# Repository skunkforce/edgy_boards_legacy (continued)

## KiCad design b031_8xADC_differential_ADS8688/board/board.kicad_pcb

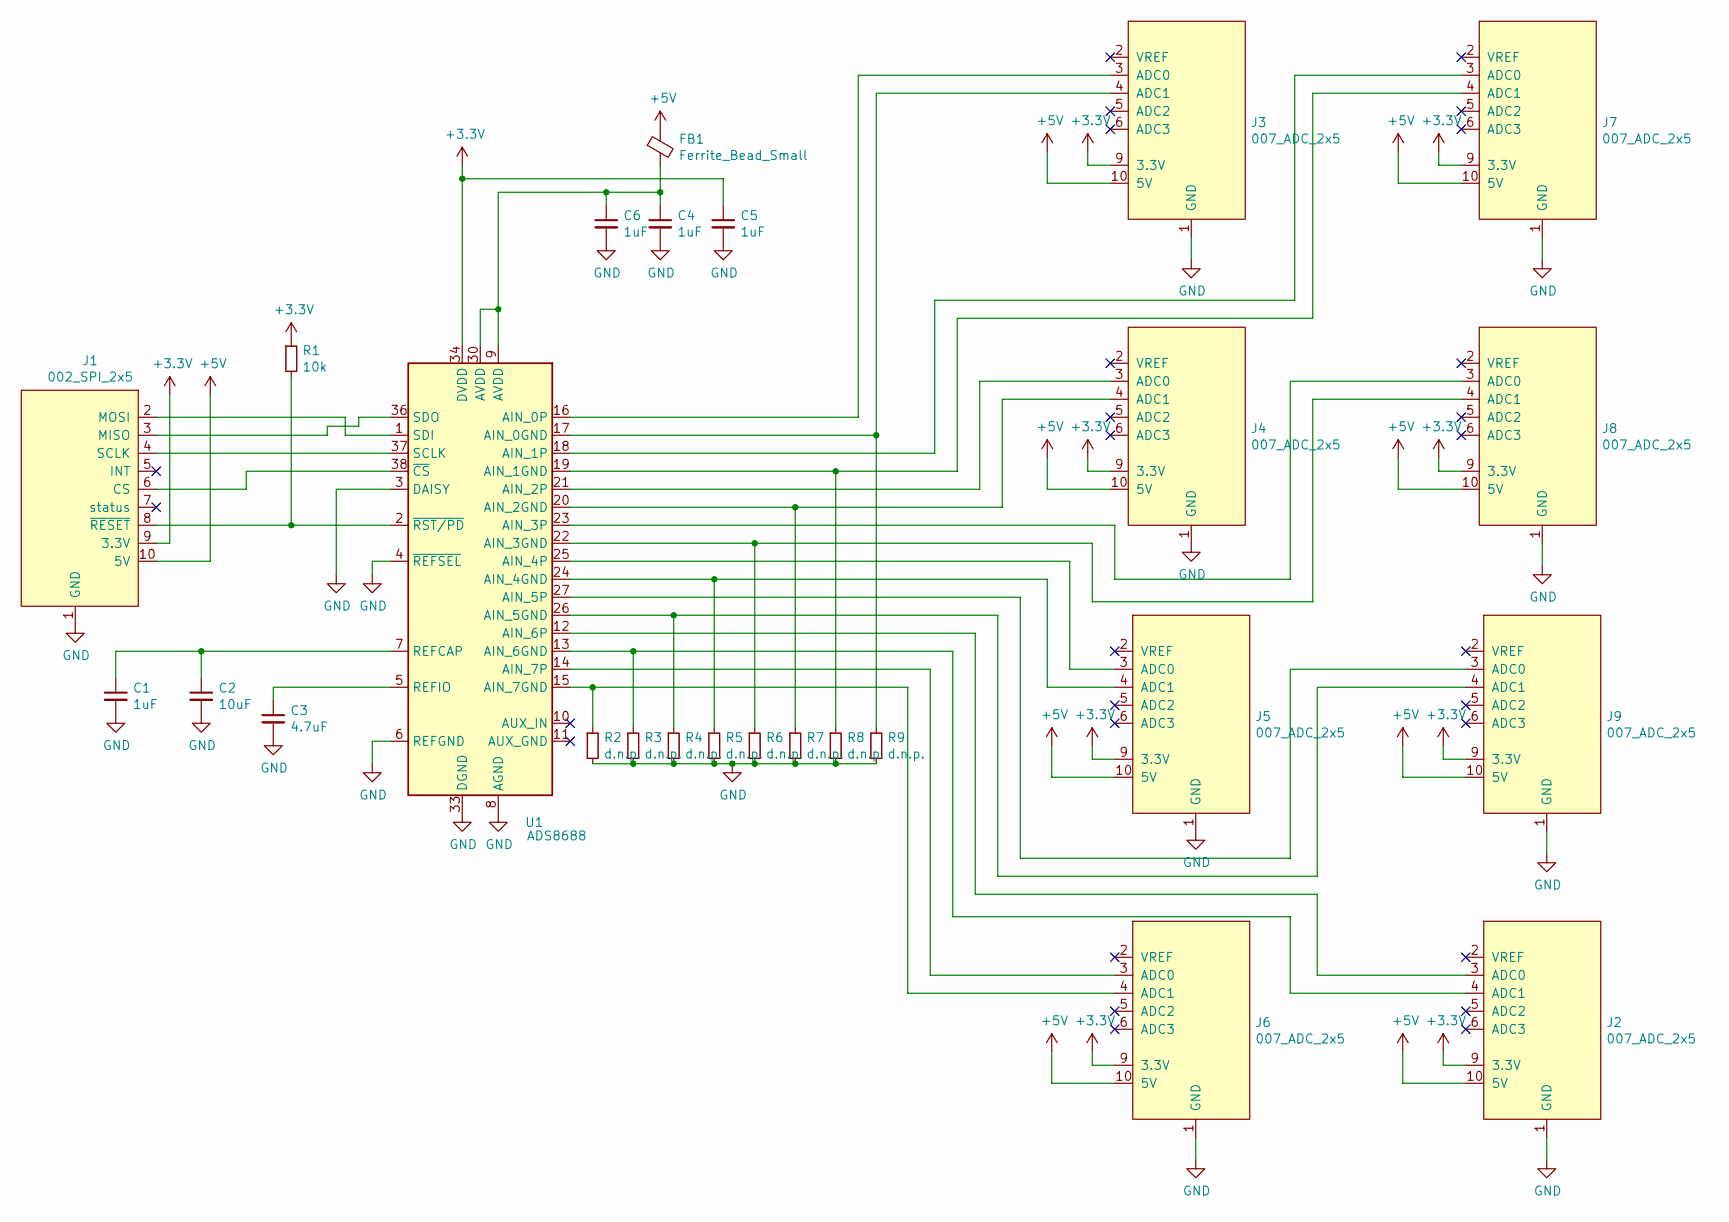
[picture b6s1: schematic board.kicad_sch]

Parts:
C1, C4, C5, C6: 1uF; C_0603_1608Metric
C2: 10uF; C_0603_1608Metric
C3: 4.7uF; C_0603_1608Metric
FB1: Ferrite_Bead_Small; L_0603_1608Metric
J1: 002_SPI_2x5; on_edge_2x05_device
J2, J3, J4, J5, J6, J7, J8, J9: 007_ADC_2x5; on_edge_2x05_host
R1: 10k; R_0603_1608Metric
R2, R3, R4, R5, R6, R7, R8, R9: d.n.p.; R_0603_1608Metric
U1: ADS8688; TSSOP-38_4.4x9.7mm_P0.5mm

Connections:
+3V3: C5.1, J1.9 (3.3V), J2.9 (3.3V), J3.9 (3.3V), J4.9 (3.3V), J5.9 (3.3V), J6.9 (3.3V), J7.9 (3.3V), J8.9 (3.3V), J9.9 (3.3V), R1.1, U1.34 (DVDD)
+5V: FB1.1, J1.10 (5V), J2.10 (5V), J3.10 (5V), J4.10 (5V), J5.10 (5V), J6.10 (5V), J7.10 (5V), J8.10 (5V), J9.10 (5V)
GND: C1.2, C2.2, C3.2, C4.2, C5.2, C6.2, J1.1 (GND), J2.1 (GND), J3.1 (GND), J4.1 (GND), J5.1 (GND), J6.1 (GND), J7.1 (GND), J8.1 (GND), J9.1 (GND), R2.2, R3.2, R4.2, R5.2, R6.2, R7.2, R8.2, R9.2, U1.3 (DAISY), U1.4 (~REFSEL), U1.6 (REFGND), U1.8 (AGND), U1.28 (AGND), U1.29 (AGND), U1.31 (AGND), U1.32 (AGND), U1.33 (DGND)
unnamed: C1.1, C2.1, U1.7 (REFCAP)
unnamed: C3.1, U1.5 (REFIO)
unnamed: C4.1, C6.1, FB1.2, U1.9 (AVDD), U1.30 (AVDD)
unnamed: J1.2 (MOSI), U1.1 (SDI)
unnamed: J1.3 (MISO), U1.36 (SDO)
unnamed: J1.4 (SCLK), U1.37 (SCLK)
unnamed: J1.6 (CS), U1.38 (~CS)
unnamed: J1.8 (~RESET), R1.2, U1.2 (~RST/PD)
unnamed: J2.3 (ADC0), U1.12 (AIN_6P)
unnamed: J2.4 (ADC1), R3.1, U1.13 (AIN_6GND)
unnamed: J3.3 (ADC0), U1.16 (AIN_0P)
unnamed: J3.4 (ADC1), R9.1, U1.17 (AIN_0GND)
unnamed: J4.3 (ADC0), U1.21 (AIN_2P)
unnamed: J4.4 (ADC1), R7.1, U1.20 (AIN_2GND)
unnamed: J5.3 (ADC0), U1.25 (AIN_4P)
unnamed: J5.4 (ADC1), R5.1, U1.24 (AIN_4GND)
unnamed: J6.3 (ADC0), U1.14 (AIN_7P)
unnamed: J6.4 (ADC1), R2.1, U1.15 (AIN_7GND)
unnamed: J7.3 (ADC0), U1.18 (AIN_1P)
unnamed: J7.4 (ADC1), R8.1, U1.19 (AIN_1GND)
unnamed: J8.3 (ADC0), U1.23 (AIN_3P)
unnamed: J8.4 (ADC1), R6.1, U1.22 (AIN_3GND)
unnamed: J9.3 (ADC0), U1.27 (AIN_5P)
unnamed: J9.4 (ADC1), R4.1, U1.26 (AIN_5GND)

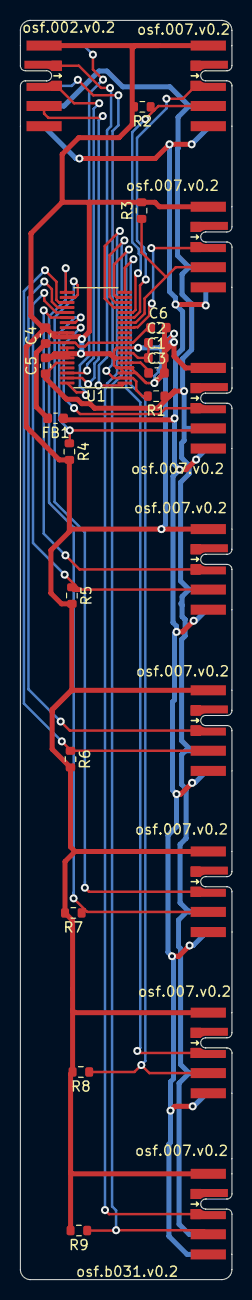
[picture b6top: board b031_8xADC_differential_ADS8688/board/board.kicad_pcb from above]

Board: 2 copper layers, 21.0 x 125.0 mm, 26 parts (0 on the bottom side), 27 nets.
